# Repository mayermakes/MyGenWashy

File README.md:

# MyGenWashy
Generic washing Machine Controller - Result of the TuttleButtle Hackathon 2025
held 13.-15.6.2025 in Vienna Austria.

the team got a broken washing machine and set the task to create a generic open source washing machine controler.
the original washing machine and its electronics and a chinese replacement board were partly reverse engineered to understand the functionality.
the team tested their theories on how safety mechanisms and machine parts worked and had to be controlled.
At the end of day two the machine was running a cold wash programm from a dev kit and some homemade electronics controlled via ESP-home.
On day three the learnings and circuits were converted into a kicad design for further testing and software development.

the board is intended to be locally produceable, by hand soldering and easy to repair. We avoided  "special" components for easy component substitution.
Unit cost is not a concerning factor, this is about the availability of a workable design that can be fitted with whatever components are available.

Thanks to Aisler for the Protoype PCBs and Farnell for supporting us with parts!

Find the Presentation PDF here:

[Hackathon EN-finial3.pdf](https://github.com/user-attachments/files/20941595/Hackathon.EN-finial3.pdf)

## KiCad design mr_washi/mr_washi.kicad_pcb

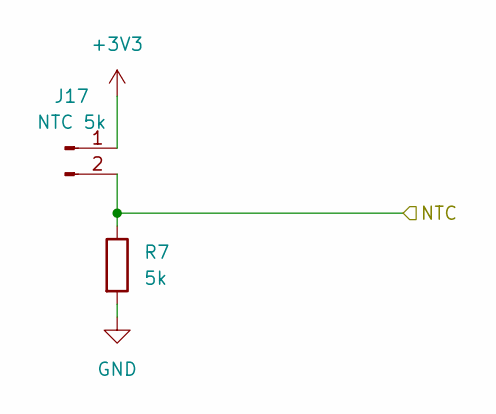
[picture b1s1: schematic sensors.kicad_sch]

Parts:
J17: NTC 5k; TerminalBlock_bornier-2_P5.08mm
R7: 5k; R_Axial_DIN0204_L3.6mm_D1.6mm_P7.62mm_Horizontal

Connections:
+3V3: J17.1; also elsewhere on the board
/MCU/7: J17.2, R7.1; also elsewhere on the board
GND: R7.2; also elsewhere on the board

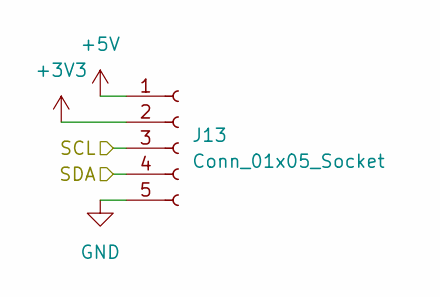
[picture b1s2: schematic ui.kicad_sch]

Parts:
J13: Conn_01x05_Socket; TerminalBlock_bornier-5_P5.08mm

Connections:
+3V3: J13.2; also elsewhere on the board
+5V: J13.1; also elsewhere on the board
/MCU/8: J13.4; also elsewhere on the board
/MCU/9: J13.3; also elsewhere on the board
GND: J13.5; also elsewhere on the board

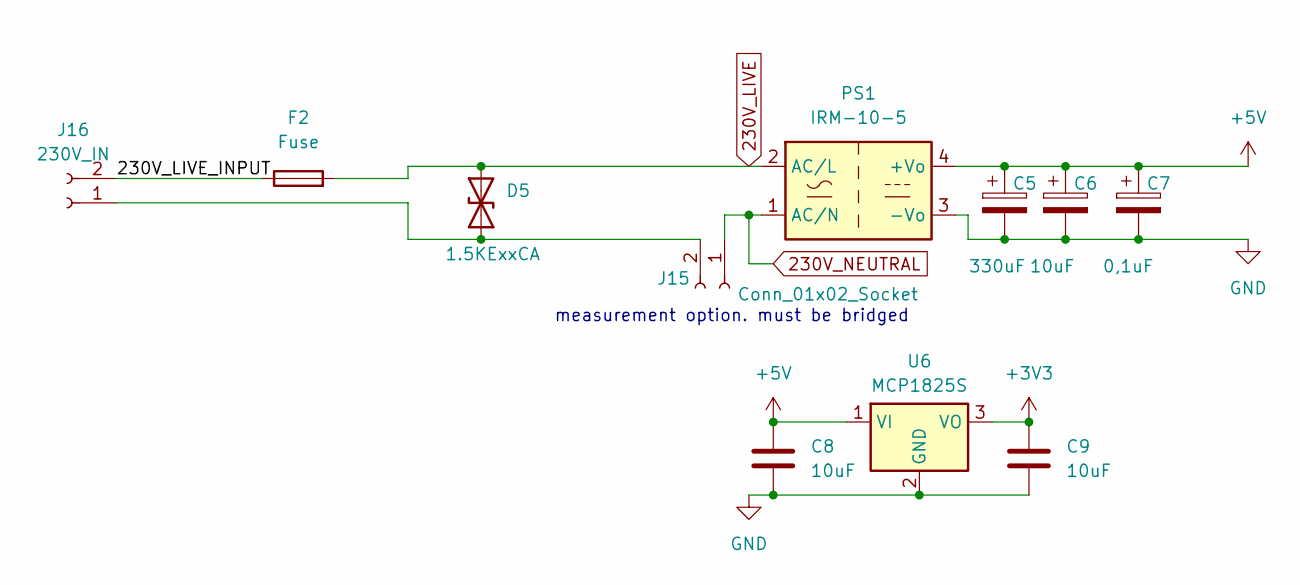
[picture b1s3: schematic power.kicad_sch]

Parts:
C5: 330uF; CP_Radial_D8.0mm_P5.00mm
C6: 10uF; CP_Radial_D7.5mm_P2.50mm
C7: 0,1uF; CP_Radial_D6.3mm_P2.50mm
C8, C9: 10uF; C_Disc_D3.0mm_W2.0mm_P2.50mm
D5: 1.5KExxCA; D_DO-201AE_P15.24mm_Horizontal
F2: Fuse; Fuseholder_Clip-5x20mm_Keystone_3512_Inline_P23.62x7.27mm_D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
J15: Conn_01x02_Socket; TerminalBlock_bornier-2_P5.08mm
J16: 230V_IN; TerminalBlock_bornier-2_P5.08mm
PS1: IRM-10-5; Converter_ACDC_MeanWell_IRM-10-xx_THT
U6: MCP1825S; SOT-223-3_TabPin2

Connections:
230V_LIVE: D5.2 (A2), F2.2, PS1.2 (AC/L); also elsewhere on the board
230V_NEUTRAL: J15.1, PS1.1 (AC/N); also elsewhere on the board
+3V3: C9.1, U6.3 (VO); also elsewhere on the board
+5V: C5.1, C6.1, C7.1, C8.1, PS1.4 (+Vo), U6.1 (VI); also elsewhere on the board
/power conversion/230V_LIVE_INPUT: F2.1, J16.2
GND: C5.2, C6.2, C7.2, C8.2, C9.2, PS1.3 (-Vo), U6.2 (GND); also elsewhere on the board
unnamed: D5.1 (A1), J15.2, J16.1

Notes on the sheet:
measurement option. must be bridged

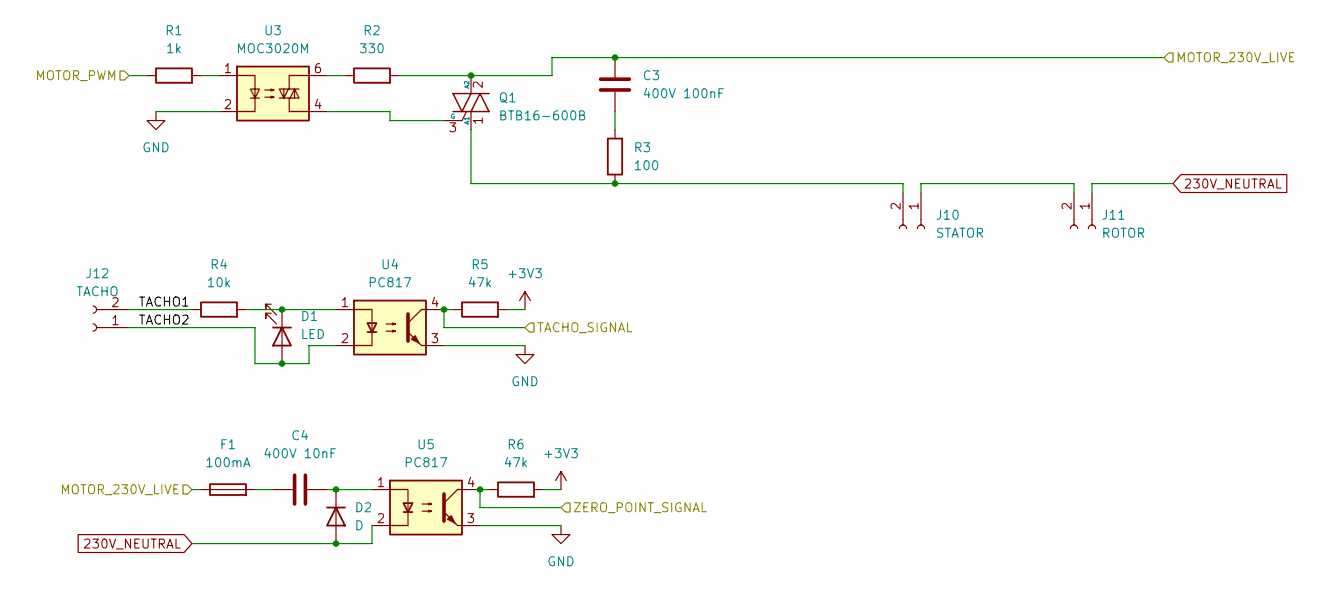
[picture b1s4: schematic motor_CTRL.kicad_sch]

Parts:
C3: 400V 100nF; C_Disc_D7.0mm_W2.5mm_P5.00mm
C4: 400V 10nF; C_Disc_D7.0mm_W2.5mm_P5.00mm
D1: LED; LED_D5.0mm
D2: D; D_T-1_P5.08mm_Horizontal
F1: 100mA; Fuseholder_Clip-5x20mm_Keystone_3512_Inline_P23.62x7.27mm_D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
J10: STATOR; TerminalBlock_bornier-2_P5.08mm
J11: ROTOR; TerminalBlock_bornier-2_P5.08mm
J12: TACHO; TerminalBlock_bornier-2_P5.08mm
Q1: BTB16-600B; TO-220-3_Vertical
R1: 1k; R_Axial_DIN0204_L3.6mm_D1.6mm_P7.62mm_Horizontal
R2: 330; R_Axial_DIN0204_L3.6mm_D1.6mm_P7.62mm_Horizontal
R3: 100; R_Axial_DIN0204_L3.6mm_D1.6mm_P7.62mm_Horizontal
R4: 10k; R_Axial_DIN0204_L3.6mm_D1.6mm_P7.62mm_Horizontal
R5, R6: 47k; R_Axial_DIN0204_L3.6mm_D1.6mm_P7.62mm_Horizontal
U3: MOC3020M; DIP-6_W7.62mm
U4, U5: PC817; DIP-4_W7.62mm

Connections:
230V_NEUTRAL: D2.2 (A), J11.1, U5.2; also elsewhere on the board
+3V3: R5.2, R6.2; also elsewhere on the board
/MCU/2: R6.1, U5.4; also elsewhere on the board
/MCU/15: R5.1, U4.4; also elsewhere on the board
/Motor control/MOTOR_230V_LIVE: C3.2, F1.1, Q1.2 (A2), R2.2; also elsewhere on the board
/Motor control/MOTOR_PWM: R1.1; also elsewhere on the board
/Motor control/TACHO1: J12.2, R4.1
/Motor control/TACHO2: D1.2 (A), J12.1, U4.2
GND: U3.2, U4.3, U5.3; also elsewhere on the board
unnamed: C3.1, R3.2
unnamed: C4.1, F1.2
unnamed: D1.1 (K), R4.2, U4.1
unnamed: C4.2, D2.1 (K), U5.1
unnamed: J10.1, J11.2
unnamed: J10.2, Q1.1 (A1), R3.1
unnamed: Q1.3 (G), U3.4
unnamed: R1.2, U3.1
unnamed: R2.1, U3.6

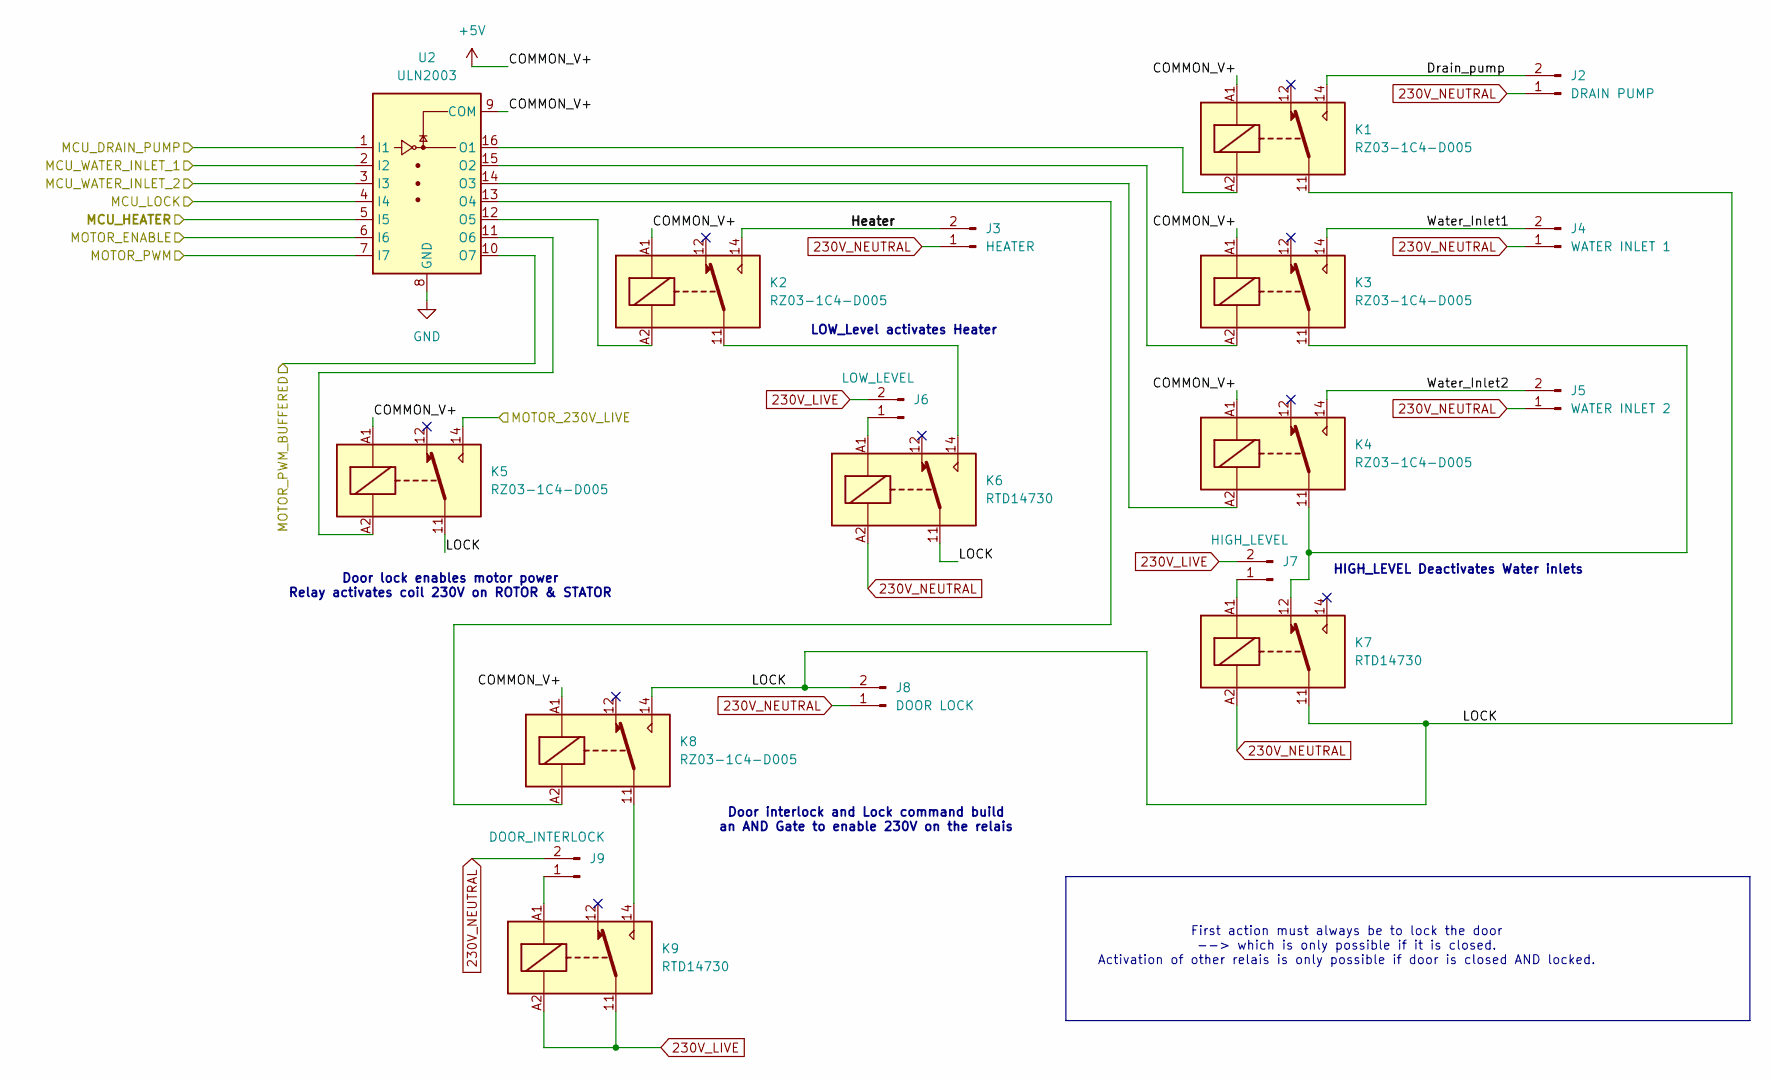
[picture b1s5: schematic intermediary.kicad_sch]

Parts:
J2: DRAIN PUMP; TerminalBlock_bornier-2_P5.08mm
J3: HEATER; TerminalBlock_bornier-2_P5.08mm
J4: WATER INLET 1; TerminalBlock_bornier-2_P5.08mm
J5: WATER INLET 2; TerminalBlock_bornier-2_P5.08mm
J6: LOW_LEVEL; TerminalBlock_bornier-2_P5.08mm
J7: HIGH_LEVEL; TerminalBlock_bornier-2_P5.08mm
J8: DOOR LOCK; TerminalBlock_bornier-2_P5.08mm
J9: DOOR_INTERLOCK; TerminalBlock_bornier-2_P5.08mm
K1, K2, K3, K4, K5, K8: RZ03-1C4-D005; Relay_SPDT_Schrack-RT1-16A-FormC_RM5mm
K6, K7, K9: RTD14730; Relay_SPDT_Schrack-RT1-16A-FormC_RM5mm
U2: ULN2003; SOIC-16_3.9x9.9mm_P1.27mm

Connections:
230V_LIVE: J6.2, J7.2, K9.11, K9.A2; also elsewhere on the board
230V_NEUTRAL: J2.1, J3.1, J4.1, J5.1, J8.1, J9.2, K6.A2, K7.A2; also elsewhere on the board
+5V: K1.A1, K2.A1, K3.A1, K4.A1, K5.A1, K8.A1, U2.9 (COM); also elsewhere on the board
/MCU/0: U2.5 (I5); also elsewhere on the board
/MCU/10: U2.4 (I4); also elsewhere on the board
/MCU/11: U2.1 (I1); also elsewhere on the board
/MCU/12: U2.3 (I3); also elsewhere on the board
/MCU/13: U2.2 (I2); also elsewhere on the board
/MCU/14: U2.6 (I6); also elsewhere on the board
/MCU/16: U2.7 (I7); also elsewhere on the board
/Motor control/MOTOR_230V_LIVE: K5.14; also elsewhere on the board
/Motor control/MOTOR_PWM: U2.10 (O7); also elsewhere on the board
/intermediary/Drain_pump: J2.2, K1.14
/intermediary/Heater: J3.2, K2.14
/intermediary/LOCK: J8.2, K1.11, K5.11, K6.11, K7.11, K8.14
/intermediary/Water_Inlet1: J4.2, K3.14
/intermediary/Water_Inlet2: J5.2, K4.14
GND: U2.8 (GND); also elsewhere on the board
unnamed: J6.1, K6.A1
unnamed: J7.1, K7.A1
unnamed: J9.1, K9.A1
unnamed: K2.11, K6.14
unnamed: K3.11, K4.11, K7.12
unnamed: K8.11, K9.14
unnamed: K1.A2, U2.16 (O1)
unnamed: K3.A2, U2.15 (O2)
unnamed: K4.A2, U2.14 (O3)
unnamed: K8.A2, U2.13 (O4)
unnamed: K2.A2, U2.12 (O5)
unnamed: K5.A2, U2.11 (O6)

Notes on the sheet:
Door lock enables motor power Relay activates coil 230V on ROTOR & STATOR
HIGH_LEVEL Deactivates Water inlets
Door interlock and Lock command build an AND Gate to enable 230V on the relais
LOW_Level activates Heater
First action must always be to lock the door --> which is only possible if it is closed. Activation of other relais is only possible if door is closed AND locked.

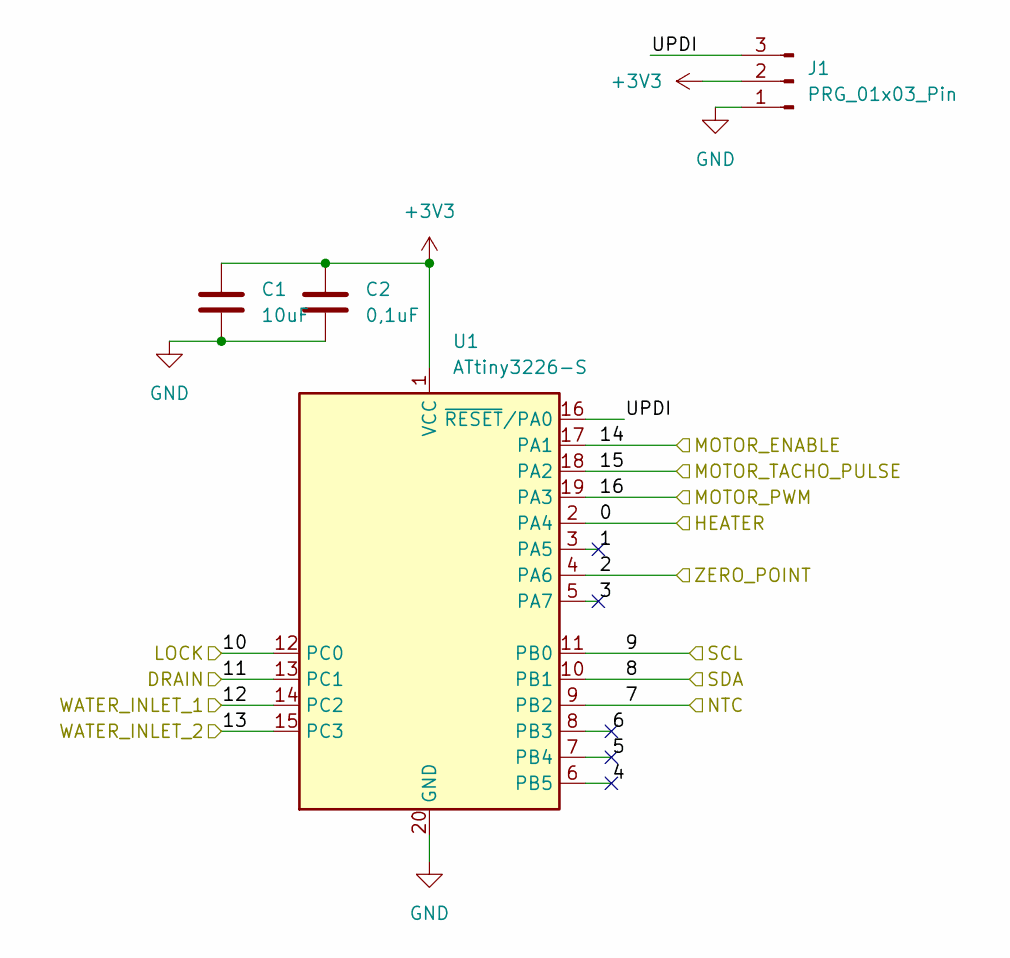
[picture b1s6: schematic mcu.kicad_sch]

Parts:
C1: 10uF; C_Disc_D3.0mm_W1.6mm_P2.50mm
C2: 0,1uF; C_Disc_D3.0mm_W1.6mm_P2.50mm
J1: PRG_01x03_Pin; PinHeader_1x03_P2.54mm_Vertical
U1: ATtiny3226-S; SOIC-20W_7.5x12.8mm_P1.27mm

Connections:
+3V3: C1.1, C2.1, J1.2, U1.1 (VCC); also elsewhere on the board
/MCU/0: U1.2 (PA4); also elsewhere on the board
/MCU/1: U1.3 (PA5)
/MCU/2: U1.4 (PA6); also elsewhere on the board
/MCU/3: U1.5 (PA7)
/MCU/4: U1.6 (PB5)
/MCU/5: U1.7 (PB4)
/MCU/6: U1.8 (PB3)
/MCU/7: U1.9 (PB2); also elsewhere on the board
/MCU/8: U1.10 (PB1); also elsewhere on the board
/MCU/9: U1.11 (PB0); also elsewhere on the board
/MCU/10: U1.12 (PC0); also elsewhere on the board
/MCU/11: U1.13 (PC1); also elsewhere on the board
/MCU/12: U1.14 (PC2); also elsewhere on the board
/MCU/13: U1.15 (PC3); also elsewhere on the board
/MCU/14: U1.17 (PA1); also elsewhere on the board
/MCU/15: U1.18 (PA2); also elsewhere on the board
/MCU/16: U1.19 (PA3); also elsewhere on the board
/MCU/UPDI: J1.3, U1.16 (~RESET/PA0)
GND: C1.2, C2.2, J1.1, U1.20 (GND); also elsewhere on the board

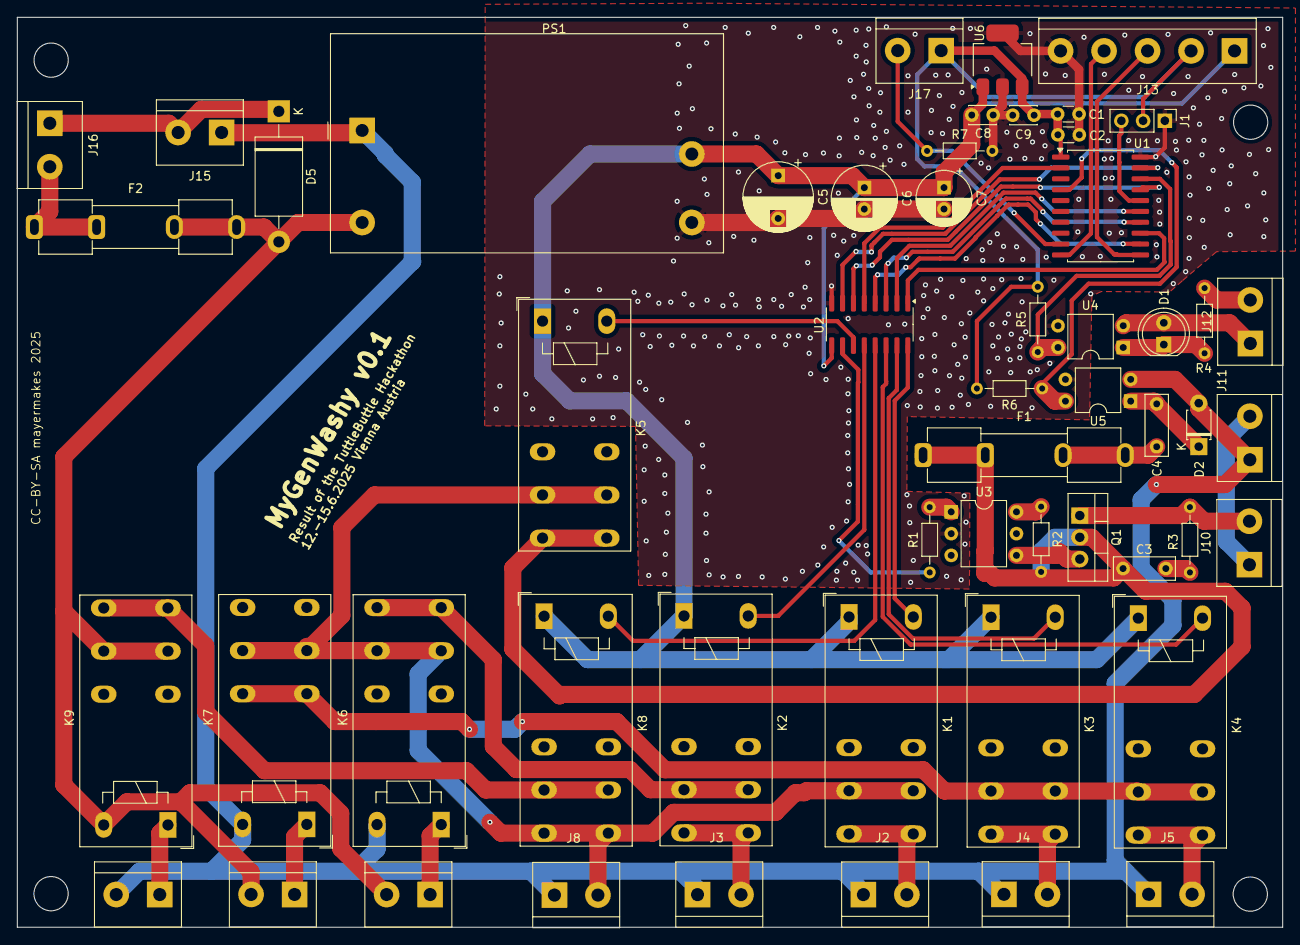
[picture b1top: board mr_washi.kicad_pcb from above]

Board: 2 copper layers, 147.8 x 106.3 mm, 54 parts (0 on the bottom side), 50 nets.

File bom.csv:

"Reference","Value","Datasheet","Footprint","Qty","DNP"
"C1,C6,C8,C9","10uF","~","-- verschiedene Werte --","4",""
"C2,C7","0,1uF","~","-- verschiedene Werte --","2",""
"C3","400V 100nF","~","Capacitor_THT:C_Disc_D7.0mm_W2.5mm_P5.00mm","1",""
"C4","400V 10nF","~","Capacitor_THT:C_Disc_D7.0mm_W2.5mm_P5.00mm","1",""
"C5","330uF","~","Capacitor_THT:CP_Radial_D8.0mm_P5.00mm","1",""
"D1","LED","~","LED_THT:LED_D5.0mm","1",""
"D2","D","~","Diode_THT:D_T-1_P5.08mm_Horizontal","1",""
"D5","1.5KExxCA","https://www.vishay.com/docs/88301/15ke.pdf","Diode_THT:D_DO-201AE_P15.24mm_Horizontal","1",""
"F1","100mA","~","Fuse:Fuseholder_Clip-5x20mm_Keystone_3512_Inline_P23.62x7.27mm_D1.02x1.57mm_Horizontal","1",""
"F2","Fuse","~","Fuse:Fuseholder_Clip-5x20mm_Keystone_3512_Inline_P23.62x7.27mm_D1.02x1.57mm_Horizontal","1",""
"J1","PRG_01x03_Pin","~","Connector_PinHeader_2.54mm:PinHeader_1x03_P2.54mm_Vertical","1",""
"J2","DRAIN PUMP","~","TerminalBlock:TerminalBlock_bornier-2_P5.08mm","1",""
"J3","HEATER","~","TerminalBlock:TerminalBlock_bornier-2_P5.08mm","1",""
"J4","WATER INLET 1","~","TerminalBlock:TerminalBlock_bornier-2_P5.08mm","1",""
"J5","WATER INLET 2","~","TerminalBlock:TerminalBlock_bornier-2_P5.08mm","1",""
"J6","LOW_LEVEL","~","TerminalBlock:TerminalBlock_bornier-2_P5.08mm","1",""
"J7","HIGH_LEVEL","~","TerminalBlock:TerminalBlock_bornier-2_P5.08mm","1",""
"J8","DOOR LOCK","~","TerminalBlock:TerminalBlock_bornier-2_P5.08mm","1",""
"J9","DOOR_INTERLOCK","~","TerminalBlock:TerminalBlock_bornier-2_P5.08mm","1",""
"J10","STATOR","~","TerminalBlock:TerminalBlock_bornier-2_P5.08mm","1",""
"J11","ROTOR","~","TerminalBlock:TerminalBlock_bornier-2_P5.08mm","1",""
"J12","TACHO","~","TerminalBlock:TerminalBlock_bornier-2_P5.08mm","1",""
"J13","Conn_01x05_Socket","~","TerminalBlock:TerminalBlock_bornier-5_P5.08mm","1",""
"J15","Conn_01x02_Socket","~","TerminalBlock:TerminalBlock_bornier-2_P5.08mm","1",""
"J16","230V_IN","~","TerminalBlock:TerminalBlock_bornier-2_P5.08mm","1",""
"J17","NTC 5k","~","TerminalBlock:TerminalBlock_bornier-2_P5.08mm","1",""
"K1,K2,K3,K4,K5,K8","RZ03-1C4-D005","https://www.te.com/commerce/DocumentDelivery/DDEController?A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","Relay_THT:Relay_SPDT_Schrack-RT1-16A-FormC_RM5mm","6",""
"K6,K7,K9","RTD14730","https://www.te.com/commerce/DocumentDelivery/DDEController?A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","Relay_THT:Relay_SPDT_Schrack-RT1-16A-FormC_RM5mm","3",""
"PS1","IRM-10-5","https://www.meanwell.com/Upload/PDF/IRM-10/IRM-10-SPEC.PDF","Converter_ACDC:Converter_ACDC_MeanWell_IRM-10-xx_THT","1",""
"Q1","BTB16-600B","https://www.st.com/resource/en/datasheet/bta16.pdf","Package_TO_SOT_THT:TO-220-3_Vertical","1",""
"R1","1k","~","Resistor_THT:R_Axial_DIN0204_L3.6mm_D1.6mm_P7.62mm_Horizontal","1",""
"R2","330","~","Resistor_THT:R_Axial_DIN0204_L3.6mm_D1.6mm_P7.62mm_Horizontal","1",""
"R3","100","~","Resistor_THT:R_Axial_DIN0204_L3.6mm_D1.6mm_P7.62mm_Horizontal","1",""
"R4","10k","~","Resistor_THT:R_Axial_DIN0204_L3.6mm_D1.6mm_P7.62mm_Horizontal","1",""
"R5,R6","47k","~","Resistor_THT:R_Axial_DIN0204_L3.6mm_D1.6mm_P7.62mm_Horizontal","2",""
"R7","5k","~","Resistor_THT:R_Axial_DIN0204_L3.6mm_D1.6mm_P7.62mm_Horizontal","1",""
"U1","ATtiny3226-S","https://ww1.microchip.com/downloads/en/DeviceDoc/ATtiny3224-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","Package_SO:SOIC-20W_7.5x12.8mm_P1.27mm","1",""
"U2","ULN2003","http://www.ti.com/lit/ds/symlink/uln2003a.pdf","Package_SO:SOIC-16_3.9x9.9mm_P1.27mm","1",""
"U3","MOC3020M","https://www.onsemi.com/pub/Collateral/MOC3023M-D.PDF","Package_DIP:DIP-6_W7.62mm","1",""
"U4,U5","PC817","http://www.soselectronic.cz/a_info/resource/d/pc817.pdf","Package_DIP:DIP-4_W7.62mm","2",""
"U6","MCP1825S","http://ww1.microchip.com/downloads/en/devicedoc/22056b.pdf","Package_TO_SOT_SMD:SOT-223-3_TabPin2","1",""

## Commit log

2025-06-15 initial upload
    Untested Board, direct result on Sunday 22:30
2025-06-17 Add BOM
2025-06-19 updated new revision
    rotated one relay, better separation of AC and 5V line,
2025-06-19 updated images
2025-06-25 BOM sourceable via Farnell
    Bom to build our First DEV units.
    High Quality parts from Farnell.com
    amounts to build 2 units + spares.
2025-06-27 Result Presentation of the Hackathon 2025
    thank you to all the supporters!

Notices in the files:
mr_washi/mr_washi.kicad_pcb:
CC-BY-SA mayermakes 2025
